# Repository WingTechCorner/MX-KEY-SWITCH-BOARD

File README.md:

# Wing's MX Switch Board

* WS2812B RGB LED
* Anti-Block/Shadow Diode
* Layout of soldering pads allows for easy COL/ROW/DATA soldering/wiring up.

# CURRENT STATUS

* Pending production parts arriving to be tested
* _Ordered_
* _Designed_

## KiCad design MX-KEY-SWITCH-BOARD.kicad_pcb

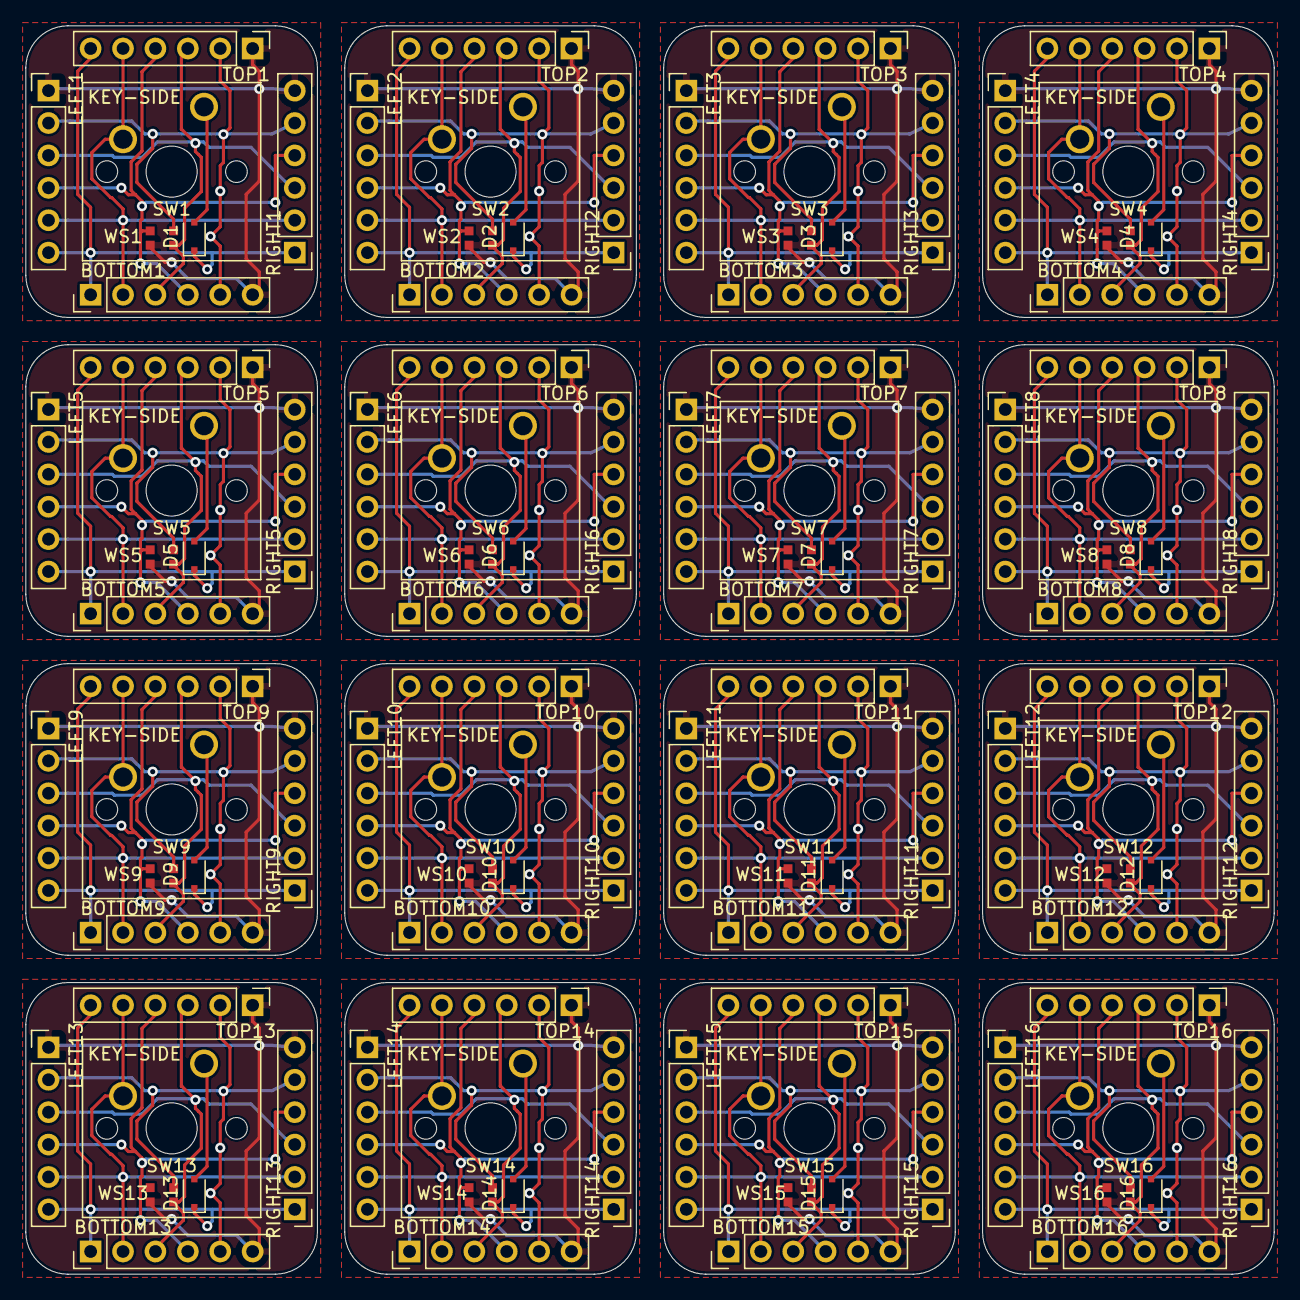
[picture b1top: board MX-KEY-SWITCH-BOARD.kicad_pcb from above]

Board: 2 copper layers, 97.9 x 97.9 mm, 112 parts (0 on the bottom side), 22 nets.

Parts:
BOTTOM1, BOTTOM2, BOTTOM3, BOTTOM4, BOTTOM5, BOTTOM6, BOTTOM7, BOTTOM8, BOTTOM9, BOTTOM10, BOTTOM11, BOTTOM12, BOTTOM13, BOTTOM14, BOTTOM15, BOTTOM16: Conn_01x06; PinHeader_1x06_P2.54mm_Vertical
D1, D2, D3, D4, D5, D6, D7, D8, D9, D10, D11, D12, D13, D14, D15, D16: Diode-SOD323F; D_SOD-323F
LEFT1, LEFT2, LEFT3, LEFT4, LEFT5, LEFT6, LEFT7, LEFT8, LEFT9, LEFT10, LEFT11, LEFT12, LEFT13, LEFT14, LEFT15, LEFT16: Conn_01x06; PinHeader_1x06_P2.54mm_Vertical
RIGHT1, RIGHT2, RIGHT3, RIGHT4, RIGHT5, RIGHT6, RIGHT7, RIGHT8, RIGHT9, RIGHT10, RIGHT11, RIGHT12, RIGHT13, RIGHT14, RIGHT15, RIGHT16: Conn_01x06; PinHeader_1x06_P2.54mm_Vertical
SW1, SW2, SW3, SW4, SW5, SW6, SW7, SW8, SW9, SW10, SW11, SW12, SW13, SW14, SW15, SW16: SW_Push; SW_Cherry_MX_1.00u_PCB
TOP1, TOP2, TOP3, TOP4, TOP5, TOP6, TOP7, TOP8, TOP9, TOP10, TOP11, TOP12, TOP13, TOP14, TOP15, TOP16: Conn_01x06; PinHeader_1x06_P2.54mm_Vertical
WS1, WS2, WS3, WS4, WS5, WS6, WS7, WS8, WS9, WS10, WS11, WS12, WS13, WS14, WS15, WS16: WS2812B-2020-JLCPCB; ws2812b-2020-2.0mmx2.0mm

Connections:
COL: BOTTOM1.2, BOTTOM2.2, BOTTOM3.2, BOTTOM4.2, BOTTOM5.2, BOTTOM6.2, BOTTOM7.2, BOTTOM8.2, BOTTOM9.2, BOTTOM10.2, BOTTOM11.2, BOTTOM12.2, BOTTOM13.2, BOTTOM14.2, BOTTOM15.2, BOTTOM16.2, LEFT1.5, LEFT2.5, LEFT3.5, LEFT4.5, LEFT5.5, LEFT6.5, LEFT7.5, LEFT8.5, LEFT9.5, LEFT10.5, LEFT11.5, LEFT12.5, LEFT13.5, LEFT14.5, LEFT15.5, LEFT16.5, RIGHT1.2, RIGHT2.2, RIGHT3.2, RIGHT4.2, RIGHT5.2, RIGHT6.2, RIGHT7.2, RIGHT8.2, RIGHT9.2, RIGHT10.2, RIGHT11.2, RIGHT12.2, RIGHT13.2, RIGHT14.2, RIGHT15.2, RIGHT16.2, SW1.2, SW2.2, SW3.2, SW4.2, SW5.2, SW6.2, SW7.2, SW8.2, SW9.2, SW10.2, SW11.2, SW12.2, SW13.2, SW14.2, SW15.2, SW16.2, TOP1.5, TOP2.5, TOP3.5, TOP4.5, TOP5.5, TOP6.5, TOP7.5, TOP8.5, TOP9.5, TOP10.5, TOP11.5, TOP12.5, TOP13.5, TOP14.5, TOP15.5, TOP16.5
DI: BOTTOM1.4, BOTTOM2.4, BOTTOM3.4, BOTTOM4.4, BOTTOM5.4, BOTTOM6.4, BOTTOM7.4, BOTTOM8.4, BOTTOM9.4, BOTTOM10.4, BOTTOM11.4, BOTTOM12.4, BOTTOM13.4, BOTTOM14.4, BOTTOM15.4, BOTTOM16.4, LEFT1.4, LEFT2.4, LEFT3.4, LEFT4.4, LEFT5.4, LEFT6.4, LEFT7.4, LEFT8.4, LEFT9.4, LEFT10.4, LEFT11.4, LEFT12.4, LEFT13.4, LEFT14.4, LEFT15.4, LEFT16.4, RIGHT1.4, RIGHT2.4, RIGHT3.4, RIGHT4.4, RIGHT5.4, RIGHT6.4, RIGHT7.4, RIGHT8.4, RIGHT9.4, RIGHT10.4, RIGHT11.4, RIGHT12.4, RIGHT13.4, RIGHT14.4, RIGHT15.4, RIGHT16.4, TOP1.4, TOP2.4, TOP3.4, TOP4.4, TOP5.4, TOP6.4, TOP7.4, TOP8.4, TOP9.4, TOP10.4, TOP11.4, TOP12.4, TOP13.4, TOP14.4, TOP15.4, TOP16.4, WS1.3, WS2.3, WS3.3, WS4.3, WS5.3, WS6.3, WS7.3, WS8.3, WS9.3, WS10.3, WS11.3, WS12.3, WS13.3, WS14.3, WS15.3, WS16.3
DO: BOTTOM1.3, BOTTOM2.3, BOTTOM3.3, BOTTOM4.3, BOTTOM5.3, BOTTOM6.3, BOTTOM7.3, BOTTOM8.3, BOTTOM9.3, BOTTOM10.3, BOTTOM11.3, BOTTOM12.3, BOTTOM13.3, BOTTOM14.3, BOTTOM15.3, BOTTOM16.3, LEFT1.3, LEFT2.3, LEFT3.3, LEFT4.3, LEFT5.3, LEFT6.3, LEFT7.3, LEFT8.3, LEFT9.3, LEFT10.3, LEFT11.3, LEFT12.3, LEFT13.3, LEFT14.3, LEFT15.3, LEFT16.3, RIGHT1.3, RIGHT2.3, RIGHT3.3, RIGHT4.3, RIGHT5.3, RIGHT6.3, RIGHT7.3, RIGHT8.3, RIGHT9.3, RIGHT10.3, RIGHT11.3, RIGHT12.3, RIGHT13.3, RIGHT14.3, RIGHT15.3, RIGHT16.3, TOP1.3, TOP2.3, TOP3.3, TOP4.3, TOP5.3, TOP6.3, TOP7.3, TOP8.3, TOP9.3, TOP10.3, TOP11.3, TOP12.3, TOP13.3, TOP14.3, TOP15.3, TOP16.3, WS1.1, WS2.1, WS3.1, WS4.1, WS5.1, WS6.1, WS7.1, WS8.1, WS9.1, WS10.1, WS11.1, WS12.1, WS13.1, WS14.1, WS15.1, WS16.1
GND: BOTTOM1.5, BOTTOM2.5, BOTTOM3.5, BOTTOM4.5, BOTTOM5.5, BOTTOM6.5, BOTTOM7.5, BOTTOM8.5, BOTTOM9.5, BOTTOM10.5, BOTTOM11.5, BOTTOM12.5, BOTTOM13.5, BOTTOM14.5, BOTTOM15.5, BOTTOM16.5, LEFT1.2, LEFT2.2, LEFT3.2, LEFT4.2, LEFT5.2, LEFT6.2, LEFT7.2, LEFT8.2, LEFT9.2, LEFT10.2, LEFT11.2, LEFT12.2, LEFT13.2, LEFT14.2, LEFT15.2, LEFT16.2, RIGHT1.5, RIGHT2.5, RIGHT3.5, RIGHT4.5, RIGHT5.5, RIGHT6.5, RIGHT7.5, RIGHT8.5, RIGHT9.5, RIGHT10.5, RIGHT11.5, RIGHT12.5, RIGHT13.5, RIGHT14.5, RIGHT15.5, RIGHT16.5, TOP1.2, TOP2.2, TOP3.2, TOP4.2, TOP5.2, TOP6.2, TOP7.2, TOP8.2, TOP9.2, TOP10.2, TOP11.2, TOP12.2, TOP13.2, TOP14.2, TOP15.2, TOP16.2, WS1.2, WS2.2, WS3.2, WS4.2, WS5.2, WS6.2, WS7.2, WS8.2, WS9.2, WS10.2, WS11.2, WS12.2, WS13.2, WS14.2, WS15.2, WS16.2
unnamed: D1.2, SW1.1
unnamed: D2.2, SW2.1
unnamed: D3.2, SW3.1
unnamed: D4.2, SW4.1
unnamed: D5.2, SW5.1
unnamed: D6.2, SW6.1
unnamed: D7.2, SW7.1
unnamed: D8.2, SW8.1
unnamed: D9.2, SW9.1
unnamed: D10.2, SW10.1
unnamed: D11.2, SW11.1
unnamed: D12.2, SW12.1
unnamed: D13.2, SW13.1
unnamed: D14.2, SW14.1
unnamed: D15.2, SW15.1
unnamed: D16.2, SW16.1
ROW: BOTTOM1.1, BOTTOM2.1, BOTTOM3.1, BOTTOM4.1, BOTTOM5.1, BOTTOM6.1, BOTTOM7.1, BOTTOM8.1, BOTTOM9.1, BOTTOM10.1, BOTTOM11.1, BOTTOM12.1, BOTTOM13.1, BOTTOM14.1, BOTTOM15.1, BOTTOM16.1, D1.1, D2.1, D3.1, D4.1, D5.1, D6.1, D7.1, D8.1, D9.1, D10.1, D11.1, D12.1, D13.1, D14.1, D15.1, D16.1, LEFT1.6, LEFT2.6, LEFT3.6, LEFT4.6, LEFT5.6, LEFT6.6, LEFT7.6, LEFT8.6, LEFT9.6, LEFT10.6, LEFT11.6, LEFT12.6, LEFT13.6, LEFT14.6, LEFT15.6, LEFT16.6, RIGHT1.1, RIGHT2.1, RIGHT3.1, RIGHT4.1, RIGHT5.1, RIGHT6.1, RIGHT7.1, RIGHT8.1, RIGHT9.1, RIGHT10.1, RIGHT11.1, RIGHT12.1, RIGHT13.1, RIGHT14.1, RIGHT15.1, RIGHT16.1, TOP1.6, TOP2.6, TOP3.6, TOP4.6, TOP5.6, TOP6.6, TOP7.6, TOP8.6, TOP9.6, TOP10.6, TOP11.6, TOP12.6, TOP13.6, TOP14.6, TOP15.6, TOP16.6
VCC: BOTTOM1.6, BOTTOM2.6, BOTTOM3.6, BOTTOM4.6, BOTTOM5.6, BOTTOM6.6, BOTTOM7.6, BOTTOM8.6, BOTTOM9.6, BOTTOM10.6, BOTTOM11.6, BOTTOM12.6, BOTTOM13.6, BOTTOM14.6, BOTTOM15.6, BOTTOM16.6, LEFT1.1, LEFT2.1, LEFT3.1, LEFT4.1, LEFT5.1, LEFT6.1, LEFT7.1, LEFT8.1, LEFT9.1, LEFT10.1, LEFT11.1, LEFT12.1, LEFT13.1, LEFT14.1, LEFT15.1, LEFT16.1, RIGHT1.6, RIGHT2.6, RIGHT3.6, RIGHT4.6, RIGHT5.6, RIGHT6.6, RIGHT7.6, RIGHT8.6, RIGHT9.6, RIGHT10.6, RIGHT11.6, RIGHT12.6, RIGHT13.6, RIGHT14.6, RIGHT15.6, RIGHT16.6, TOP1.1, TOP2.1, TOP3.1, TOP4.1, TOP5.1, TOP6.1, TOP7.1, TOP8.1, TOP9.1, TOP10.1, TOP11.1, TOP12.1, TOP13.1, TOP14.1, TOP15.1, TOP16.1, WS1.4, WS2.4, WS3.4, WS4.4, WS5.4, WS6.4, WS7.4, WS8.4, WS9.4, WS10.4, WS11.4, WS12.4, WS13.4, WS14.4, WS15.4, WS16.4

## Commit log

2021-09-25 init
2021-09-25 adding git ignore and README
2021-09-25 README.md
2021-10-08 Switching design to add headers to all four sides.
